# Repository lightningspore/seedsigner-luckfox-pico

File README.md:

# seedsigner-luckfox-pico
Port of the SeedSigner code to support the LuckFox Pico Linux board family. Since this device is still an embedded Linux device, like the Raspberry Pi, the changes are fairly minimal in order to access the buttons and the camera. This repo mostly pertains to the Buildroot OS build instructions, the KiCAD schematic and PCB design files, and 3D models of cases for the assembled device.

SeedSigner code fork: https://github.com/lightningspore/seedsigner/tree/0.8.5-luckfox

## Hardware Photos
_Most Recent Iteration: LuckFox Pico Mini B with no onboard SPI flash_

_Previous Iteration: LuckFox Pico Pro Max (More Flash, SPI Flash)_

## Demo Videos

### First Look: SeedSigner running on LuckFox Pico Linux devboard

## Materials Needed
Check out the shopping list for a parts list of various LuckFox-based hardware configurations: [here](docs/shopping_list.md)

These example builds can build a device for around $60.

## OS Image Build with Buildroot
The OS image is built using Buildroot in a Docker container. The complete build instructions, package requirements, and troubleshooting process are documented in [OS-build-instructions.md](docs/OS-build-instructions.md).

## Dev Machine Setup

### Install ADB
Developing for the LuckFox Pico device is quite convenient since the devices never connect to the internet and you can access the device shell using `adb`. You can push files back and forth to your dev machine, and you can access the device as a shell easily.
```
# mac
brew install homebrew/cask/android-platform-tools

# linux
sudo apt install android-tools-adb
```

### ADB Connection and Device Management

1. Connect to the device:
```
# List connected devices
adb devices

# Connect to device shell
adb shell
```

2. File Operations:
```
# Push files to device
adb push local_file.txt /remote/path/

# Sync the code repo for local development
adb push /repos/seedsigner/src /seedsigner

# Pull files from device
adb pull /seedsigner/config.json .

# List files on device
adb shell ls /path/to/directory
```

## Hardware Identification
Notice the left device has an empty PCB footprint pattern on it. This is where the optional SPI flash is soldered on. For the SeedSigner project we don't want permanent storage, so avoid devices with soldered SPI flash.

```
LEFT:  LuckFox Pico Mini A -> No Flash
RIGHT: LuckFox Pico Mini B -> Soldered Flash
```

## Flashing the Device

### Flash MicroSD Card
```
sudo dd bs=4M status=progress if=seedsigner-luckfox-pico-YYYYmmdd_hhmmss.img of=/dev/diskX
```
Replace `/dev/diskX` with your actual SD card device path.

## LuckFox Pico OS Modifications
We have forked the [LuckFox Pico SDK](https://github.com/lightningspore/luckfox-pico) in order to enable various hardware features like pull-up resistors, adjust video RAM, and other things.

### Camera Memory
The LuckFox devotes some of its memory for camera-related algorithms, but we don't use this feature. Particularly on the LuckFox Pico Mini device, which only has 64MB of RAM, it is beneficial for us to reclaim a bit of this memory.

Memory usage WITHOUT modification:
```bash
[root@luckfox ]# free -h
              total        used        free      shared  buff/cache   available
Mem:          33.0M       24.3M        1.4M      476.0K        7.3M        5.4M
Swap:             0           0           0
```

Memory usage WITH modification:
```bash
[root@luckfox ]# free -h
              total        used        free      shared  buff/cache   available
Mem:          53.0M       23.6M        1.9M      472.0K       27.5M       25.3M
Swap:             0           0           0
```

### Pull-up Resistors
Our current dev board has external pull-up resistors, since we didn't know how to enable these at the time, and it is always smart to plan ahead when designing PCBs. NOTE: Even with this commit and this change, the internal pull-ups don't seem to work.

### SPI Buffer Size
While it is possible to send SPI data in chunks, you can increase the SPI buffer size to slightly increase throughput, which is useful for larger displays.

### PWM Output
In order to control the LCD screen backlight and support true dimming of the display (instead of just changing the background color of the QR code, for example), we had to enable a PWM on a specific output pin.

## Support the Developer
If you find this project helpful and would like to support its development, you can buy me a coffee! Your support helps keep this project going and funds future improvements. Help decentralize Bitcoin hardware!

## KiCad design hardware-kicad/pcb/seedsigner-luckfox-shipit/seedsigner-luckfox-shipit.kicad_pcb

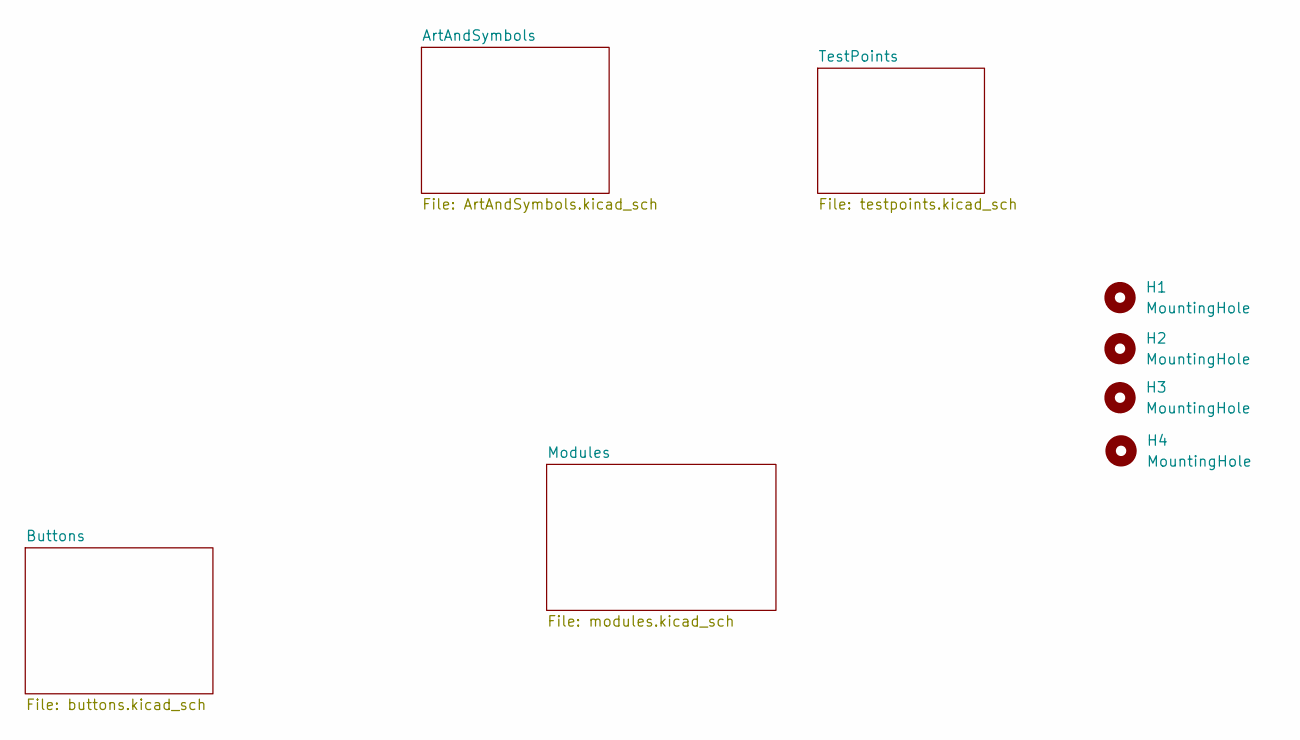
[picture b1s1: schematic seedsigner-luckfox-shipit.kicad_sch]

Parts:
H1, H2, H3, H4: MountingHole; MOUNT_HOLE_3MM

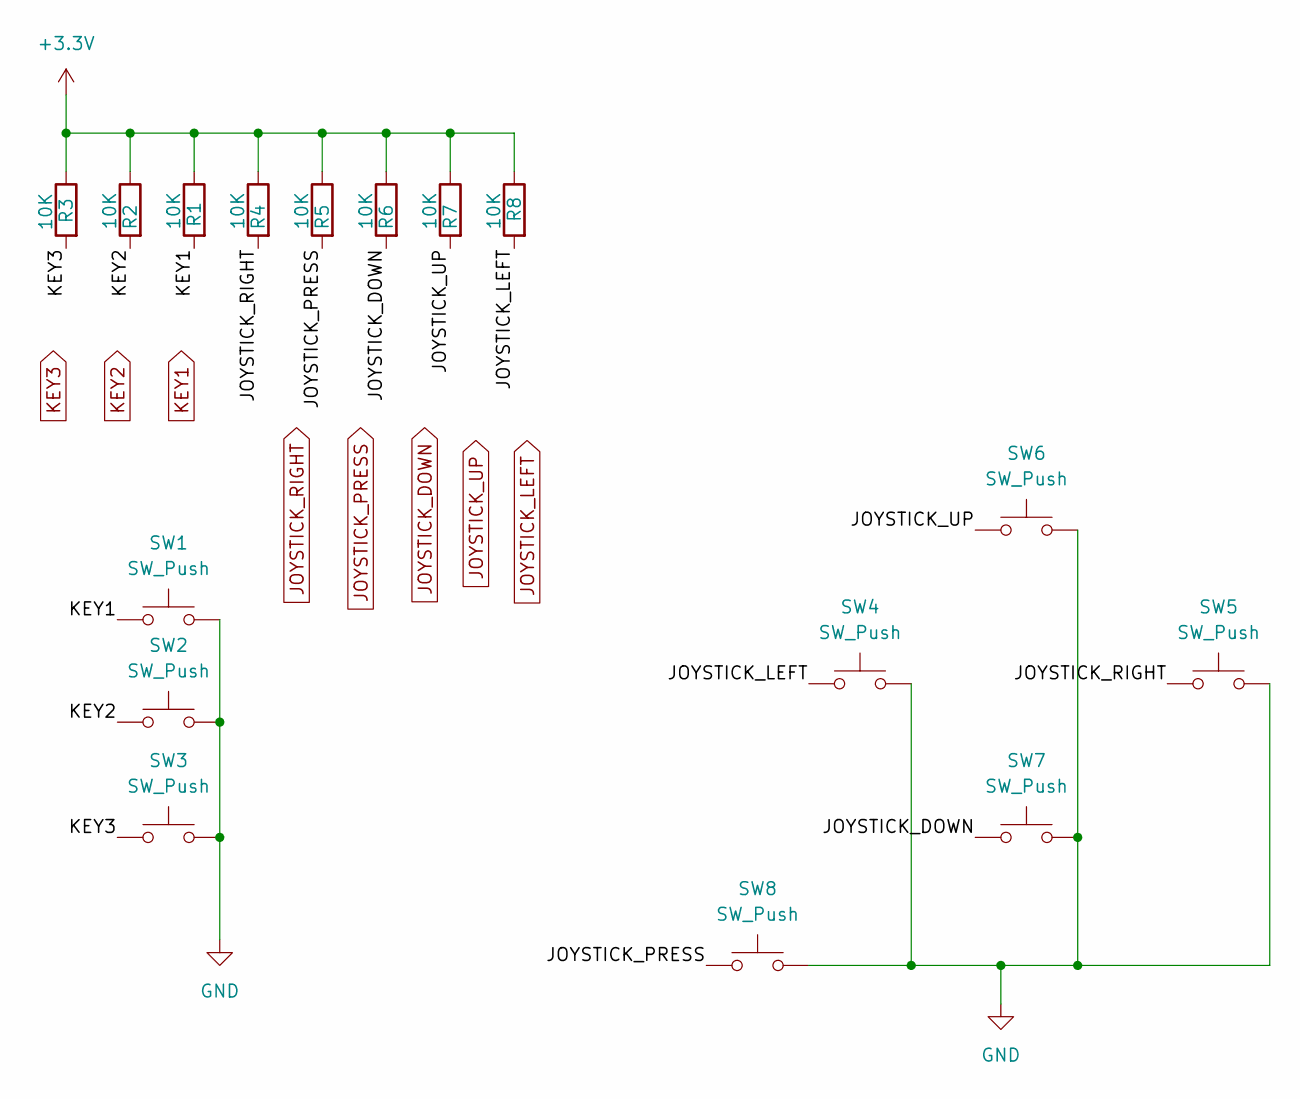
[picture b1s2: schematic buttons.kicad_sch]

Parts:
R1, R2, R3, R4, R5, R6, R7, R8: 10K; R_0805_2012Metric_Pad1.20x1.40mm_HandSolder
SW1, SW2, SW3, SW4, SW5, SW6, SW7, SW8: SW_Push; BTN_SPST_NO_PTH

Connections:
+3.3V: R1.1, R2.1, R3.1, R4.1, R5.1, R6.1, R7.1, R8.1; also elsewhere on the board
GND: SW1.2, SW2.2, SW3.2, SW4.2, SW5.2, SW6.2, SW7.2, SW8.2; also elsewhere on the board
JOYSTICK_DOWN: R6.2, SW7.1; also elsewhere on the board
JOYSTICK_LEFT: R8.2, SW4.1; also elsewhere on the board
JOYSTICK_PRESS: R5.2, SW8.1; also elsewhere on the board
JOYSTICK_RIGHT: R4.2, SW5.1; also elsewhere on the board
JOYSTICK_UP: R7.2, SW6.1; also elsewhere on the board
KEY1: R1.2, SW1.1; also elsewhere on the board
KEY2: R2.2, SW2.1; also elsewhere on the board
KEY3: R3.2, SW3.1; also elsewhere on the board

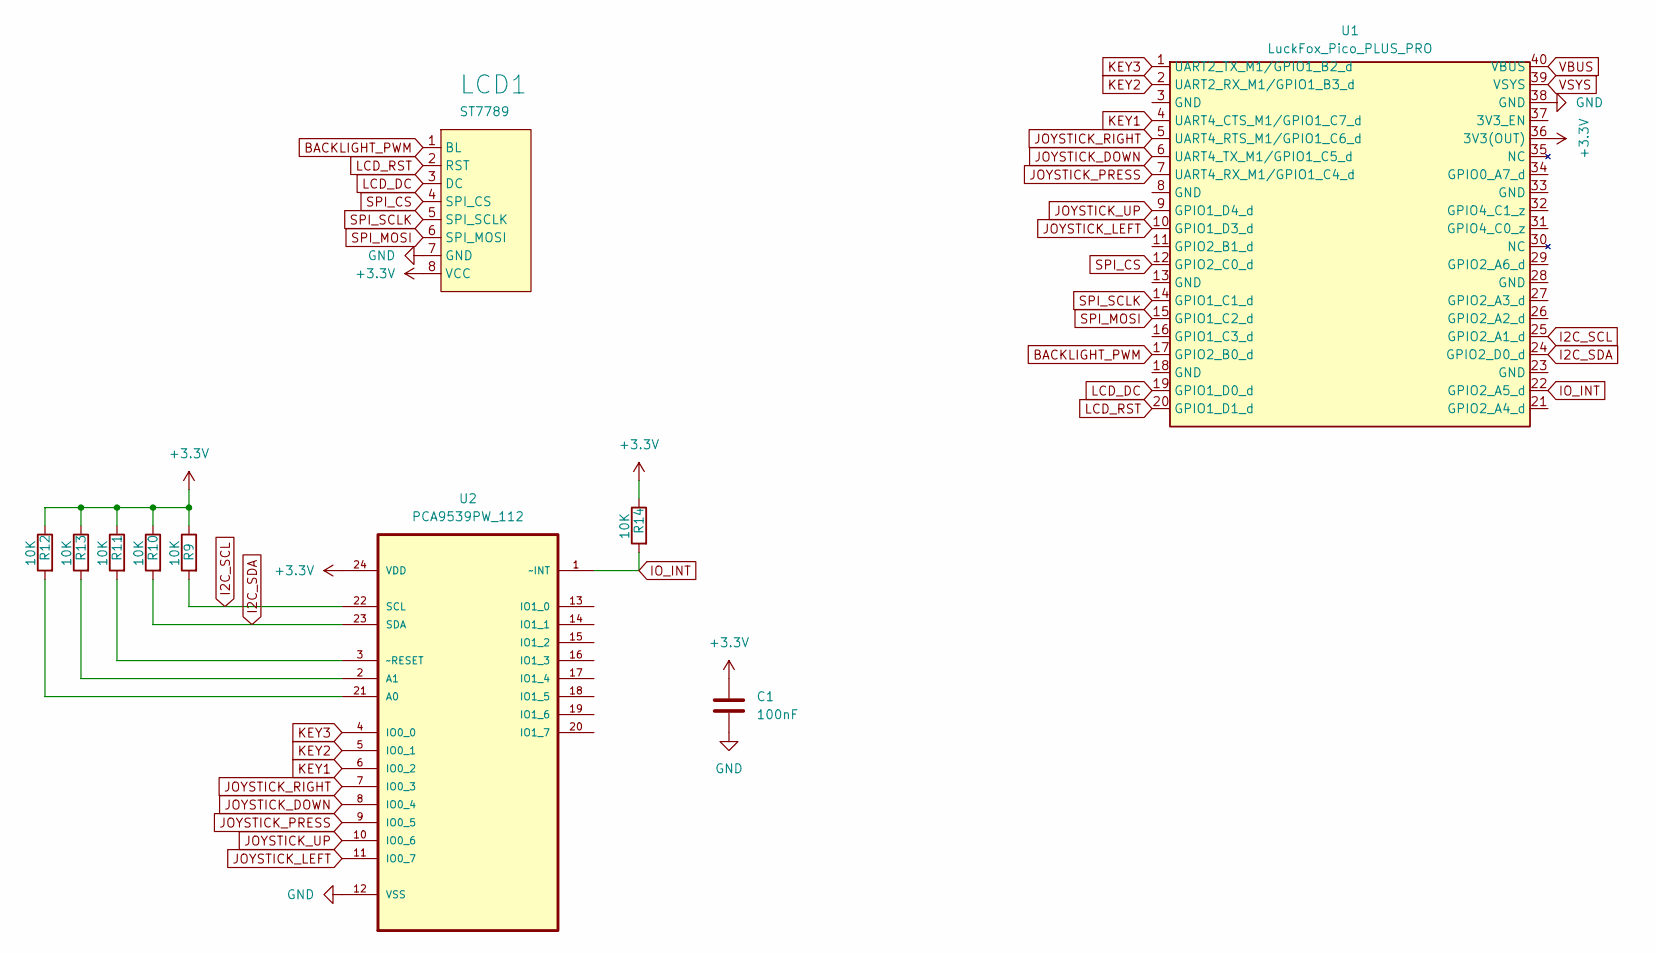
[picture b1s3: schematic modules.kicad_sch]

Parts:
C1: 100nF; C_0805_2012Metric_Pad1.18x1.45mm_HandSolder
LCD1: ST7789; ST7789_LCD_MOD1
R9, R10, R11, R12, R13, R14: 10K; R_0805_2012Metric_Pad1.20x1.40mm_HandSolder
U1: LuckFox_Pico_PLUS_PRO; LUCKFOX_PICO
U2: PCA9539PW_112; SOP65P640X110-24N; MPN PCA9539PW,112

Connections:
+3.3V: C1.1, LCD1.8 (VCC), R9.1, R10.1, R11.1, R12.1, R13.1, R14.1, U1.36 (3V3(OUT)), U2.24 (VDD); also elsewhere on the board
BACKLIGHT_PWM: LCD1.1 (BL), U1.17 (GPIO2_B0_d)
GND: C1.2, LCD1.7 (GND), U1.38 (GND), U2.12 (VSS); also elsewhere on the board
I2C_SCL: R9.2, U1.25 (GPIO2_A1_d), U2.22 (SCL)
I2C_SDA: R10.2, U1.24 (GPIO2_D0_d), U2.23 (SDA)
IO_INT: R14.2, U1.22 (GPIO2_A5_d), U2.1 (~INT)
JOYSTICK_DOWN: U1.6 (UART4_TX_M1/GPIO1_C5_d), U2.8 (IO0_4); also elsewhere on the board
JOYSTICK_LEFT: U1.10 (GPIO1_D3_d), U2.11 (IO0_7); also elsewhere on the board
JOYSTICK_PRESS: U1.7 (UART4_RX_M1/GPIO1_C4_d), U2.9 (IO0_5); also elsewhere on the board
JOYSTICK_RIGHT: U1.5 (UART4_RTS_M1/GPIO1_C6_d), U2.7 (IO0_3); also elsewhere on the board
JOYSTICK_UP: U1.9 (GPIO1_D4_d), U2.10 (IO0_6); also elsewhere on the board
KEY1: U1.4 (UART4_CTS_M1/GPIO1_C7_d), U2.6 (IO0_2); also elsewhere on the board
KEY2: U1.2 (UART2_RX_M1/GPIO1_B3_d), U2.5 (IO0_1); also elsewhere on the board
KEY3: U1.1 (UART2_TX_M1/GPIO1_B2_d), U2.4 (IO0_0); also elsewhere on the board
LCD_DC: LCD1.3 (DC), U1.19 (GPIO1_D0_d)
LCD_RST: LCD1.2 (RST), U1.20 (GPIO1_D1_d)
unnamed: R12.2, U2.21 (A0)
unnamed: R13.2, U2.2 (A1)
unnamed: R11.2, U2.3 (~RESET)
SPI_CS: LCD1.4 (SPI_CS), U1.12 (GPIO2_C0_d)
SPI_MOSI: LCD1.6 (SPI_MOSI), U1.15 (GPIO1_C2_d)
SPI_SCLK: LCD1.5 (SPI_SCLK), U1.14 (GPIO1_C1_d)
VBUS: U1.40 (VBUS); also elsewhere on the board
VSYS: U1.39 (VSYS); also elsewhere on the board

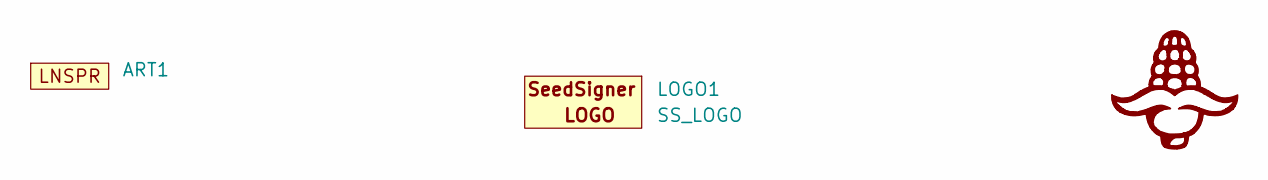
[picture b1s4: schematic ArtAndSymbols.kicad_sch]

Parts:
ART1: LightningSpore_Logo
LOGO1: SS_LOGO; seedsigner-logo-small
LOGO2: CORN-LOGO; corn-logo

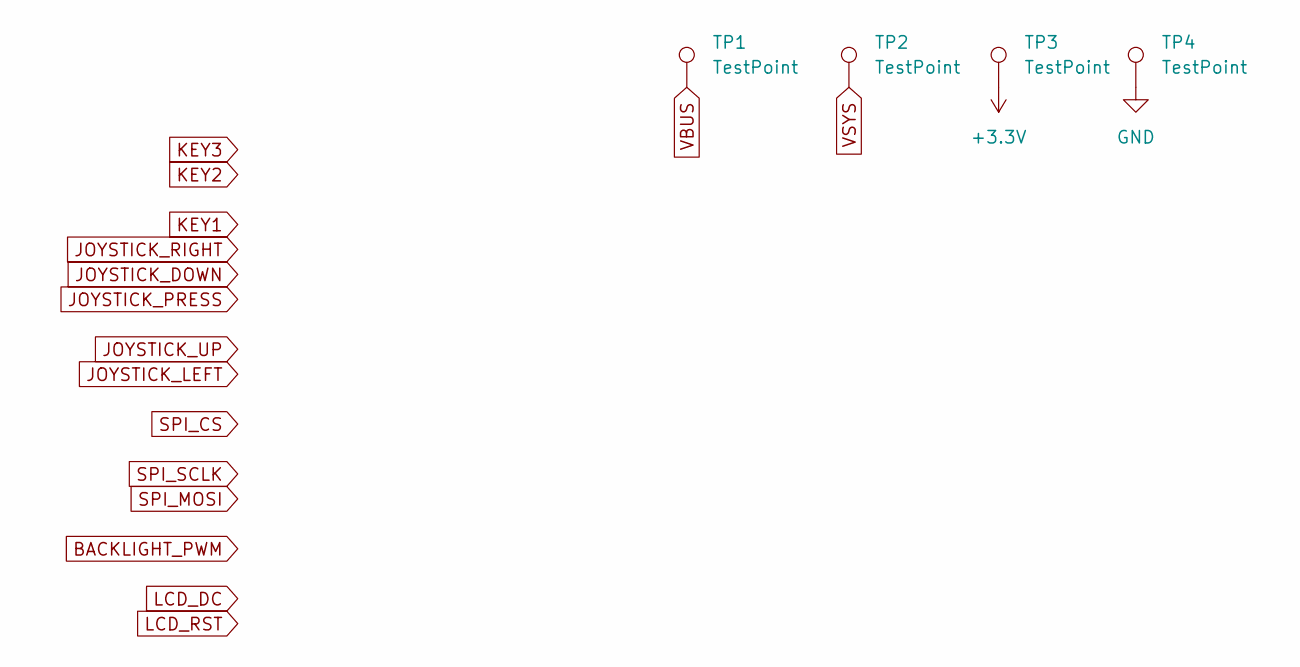
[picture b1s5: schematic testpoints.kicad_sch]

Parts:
TP1, TP2, TP3, TP4: TestPoint; TestPoint_Pad_1.5x1.5mm

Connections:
+3.3V: TP3.1; also elsewhere on the board
GND: TP4.1; also elsewhere on the board
VBUS: TP1.1; also elsewhere on the board
VSYS: TP2.1; also elsewhere on the board

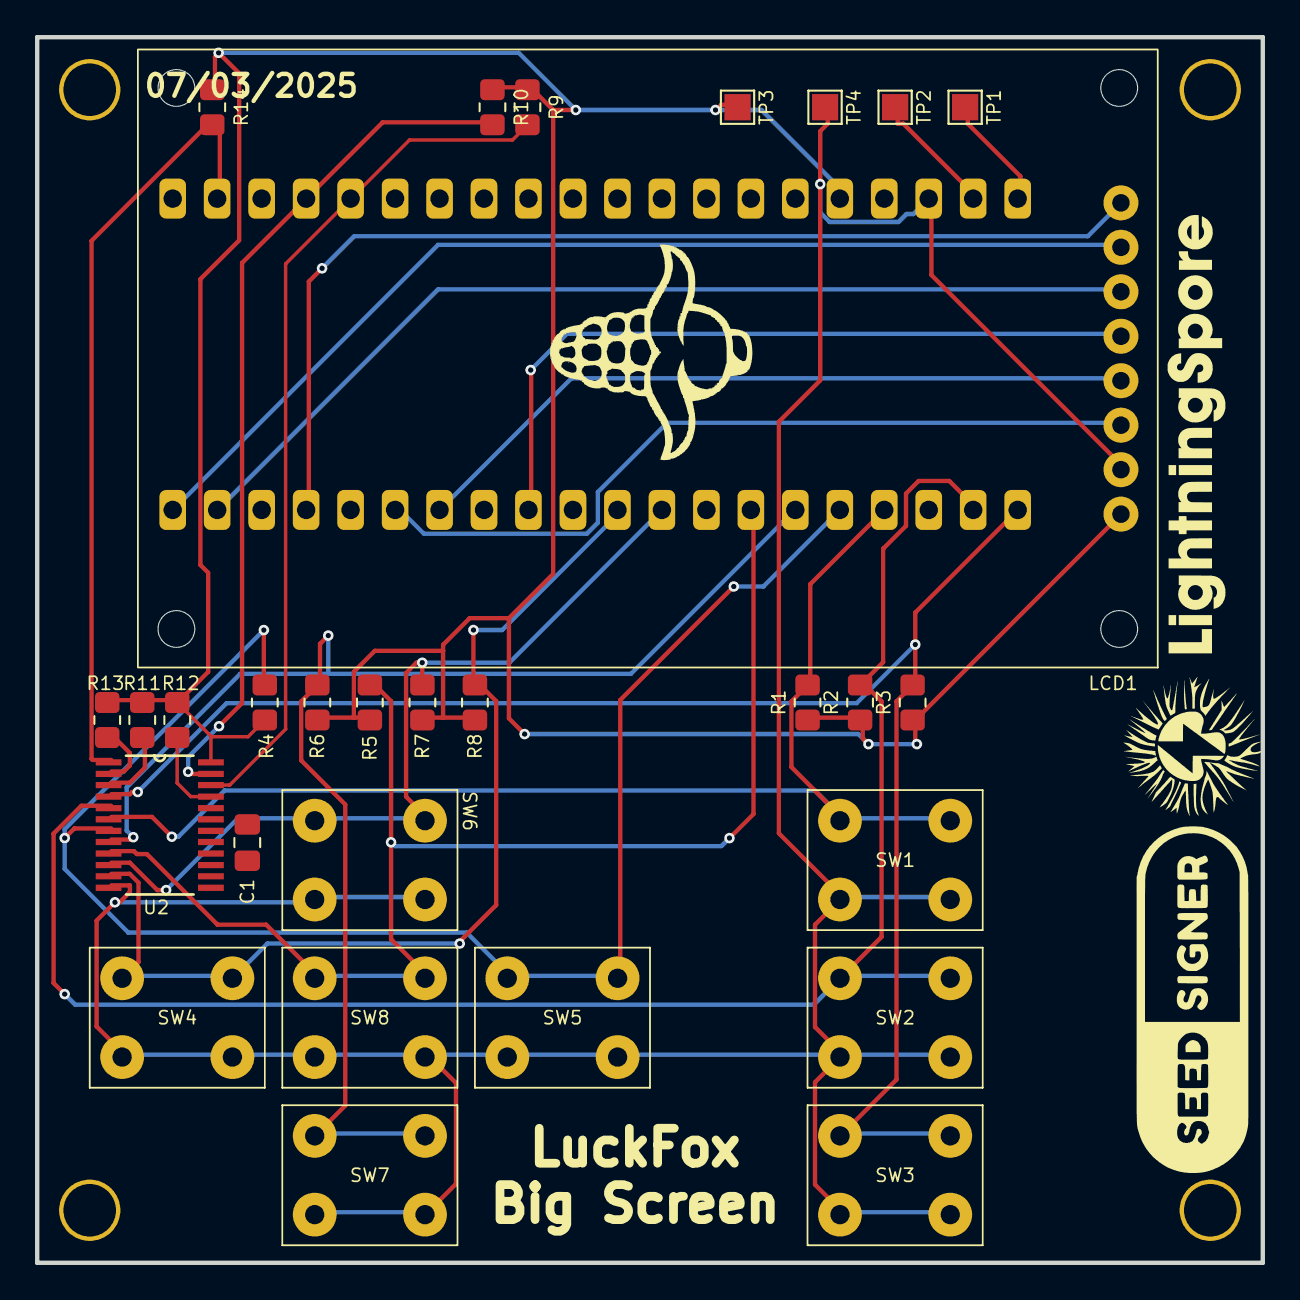
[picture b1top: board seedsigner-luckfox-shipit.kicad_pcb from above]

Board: 2 copper layers, 70.0 x 70.0 mm, 37 parts (1 on the bottom side), 24 nets.

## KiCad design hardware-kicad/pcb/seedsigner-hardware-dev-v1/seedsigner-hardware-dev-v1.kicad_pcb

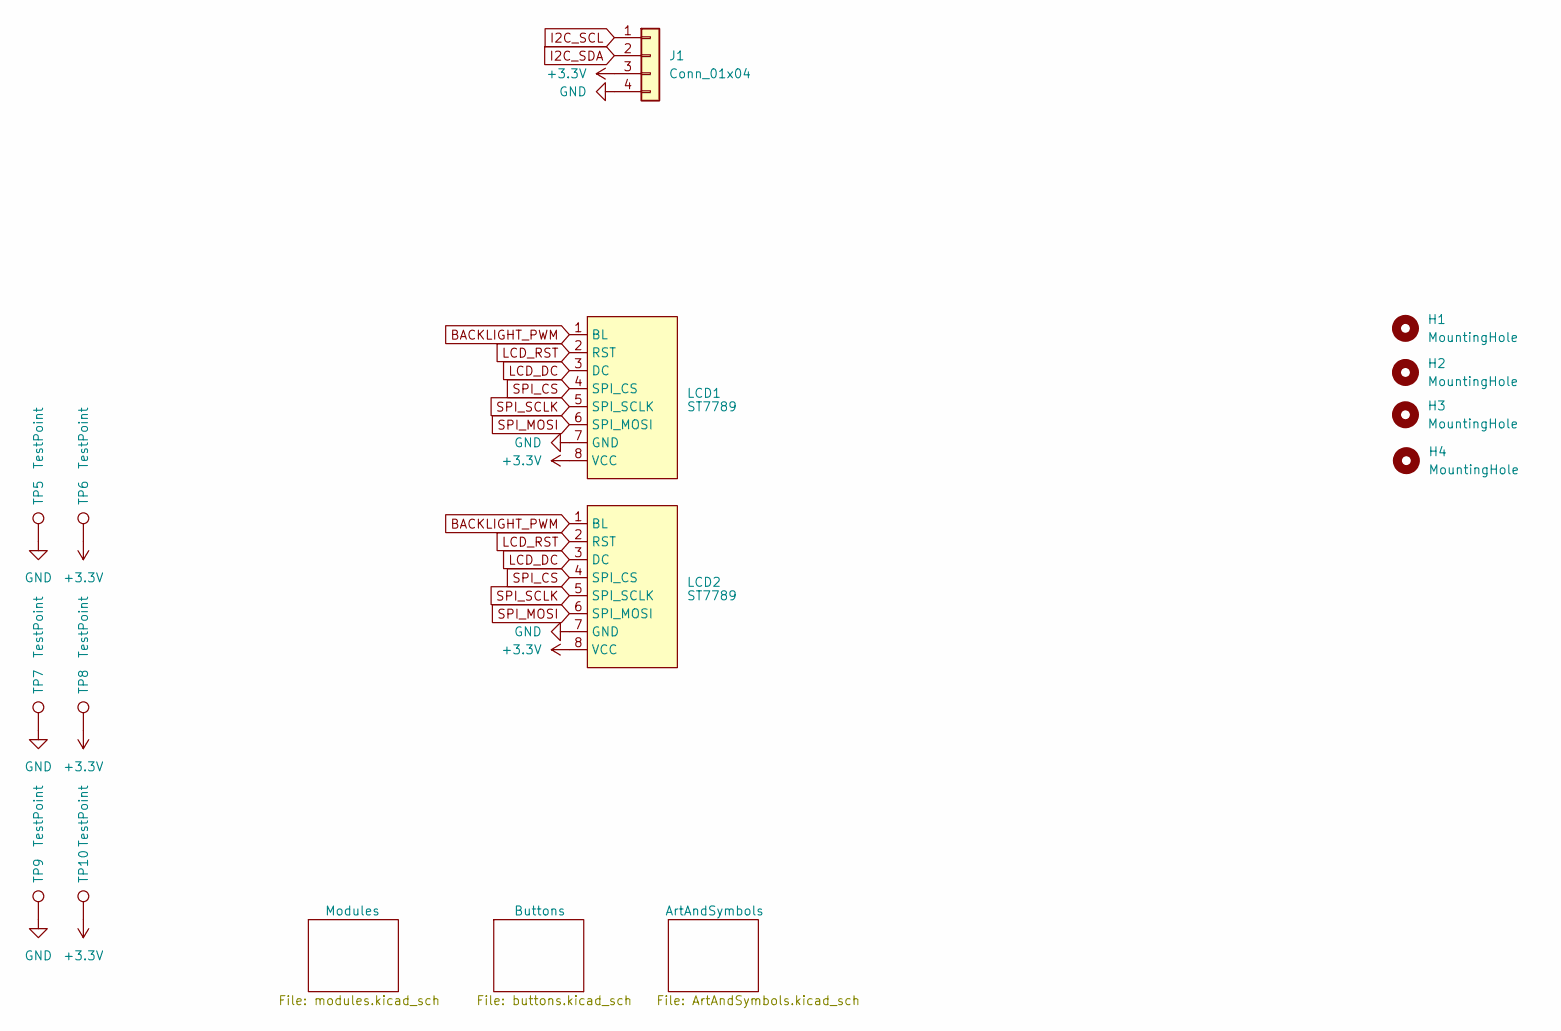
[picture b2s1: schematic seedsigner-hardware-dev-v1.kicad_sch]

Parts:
H1, H2, H3, H4: MountingHole; MOUNT_HOLE_3MM
J1: Conn_01x04; NS-Tech_Grove_1x04_P2mm_Vertical
LCD1, LCD2: ST7789; PinHeader_1x08_P2.54mm_Vertical
TP5, TP6, TP7, TP8, TP9, TP10: TestPoint; TestPoint_Pad_D1.0mm

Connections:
+3.3V: J1.3, LCD1.8 (VCC), LCD2.8 (VCC), TP6.1, TP8.1, TP10.1; also elsewhere on the board
BACKLIGHT_PWM: LCD1.1 (BL), LCD2.1 (BL); also elsewhere on the board
GND: J1.4, LCD1.7 (GND), LCD2.7 (GND), TP5.1, TP7.1, TP9.1; also elsewhere on the board
I2C_SCL: J1.1; also elsewhere on the board
I2C_SDA: J1.2; also elsewhere on the board
LCD_DC: LCD1.3 (DC), LCD2.3 (DC); also elsewhere on the board
LCD_RST: LCD1.2 (RST), LCD2.2 (RST); also elsewhere on the board
SPI_CS: LCD1.4 (SPI_CS), LCD2.4 (SPI_CS); also elsewhere on the board
SPI_MOSI: LCD1.6 (SPI_MOSI), LCD2.6 (SPI_MOSI); also elsewhere on the board
SPI_SCLK: LCD1.5 (SPI_SCLK), LCD2.5 (SPI_SCLK); also elsewhere on the board

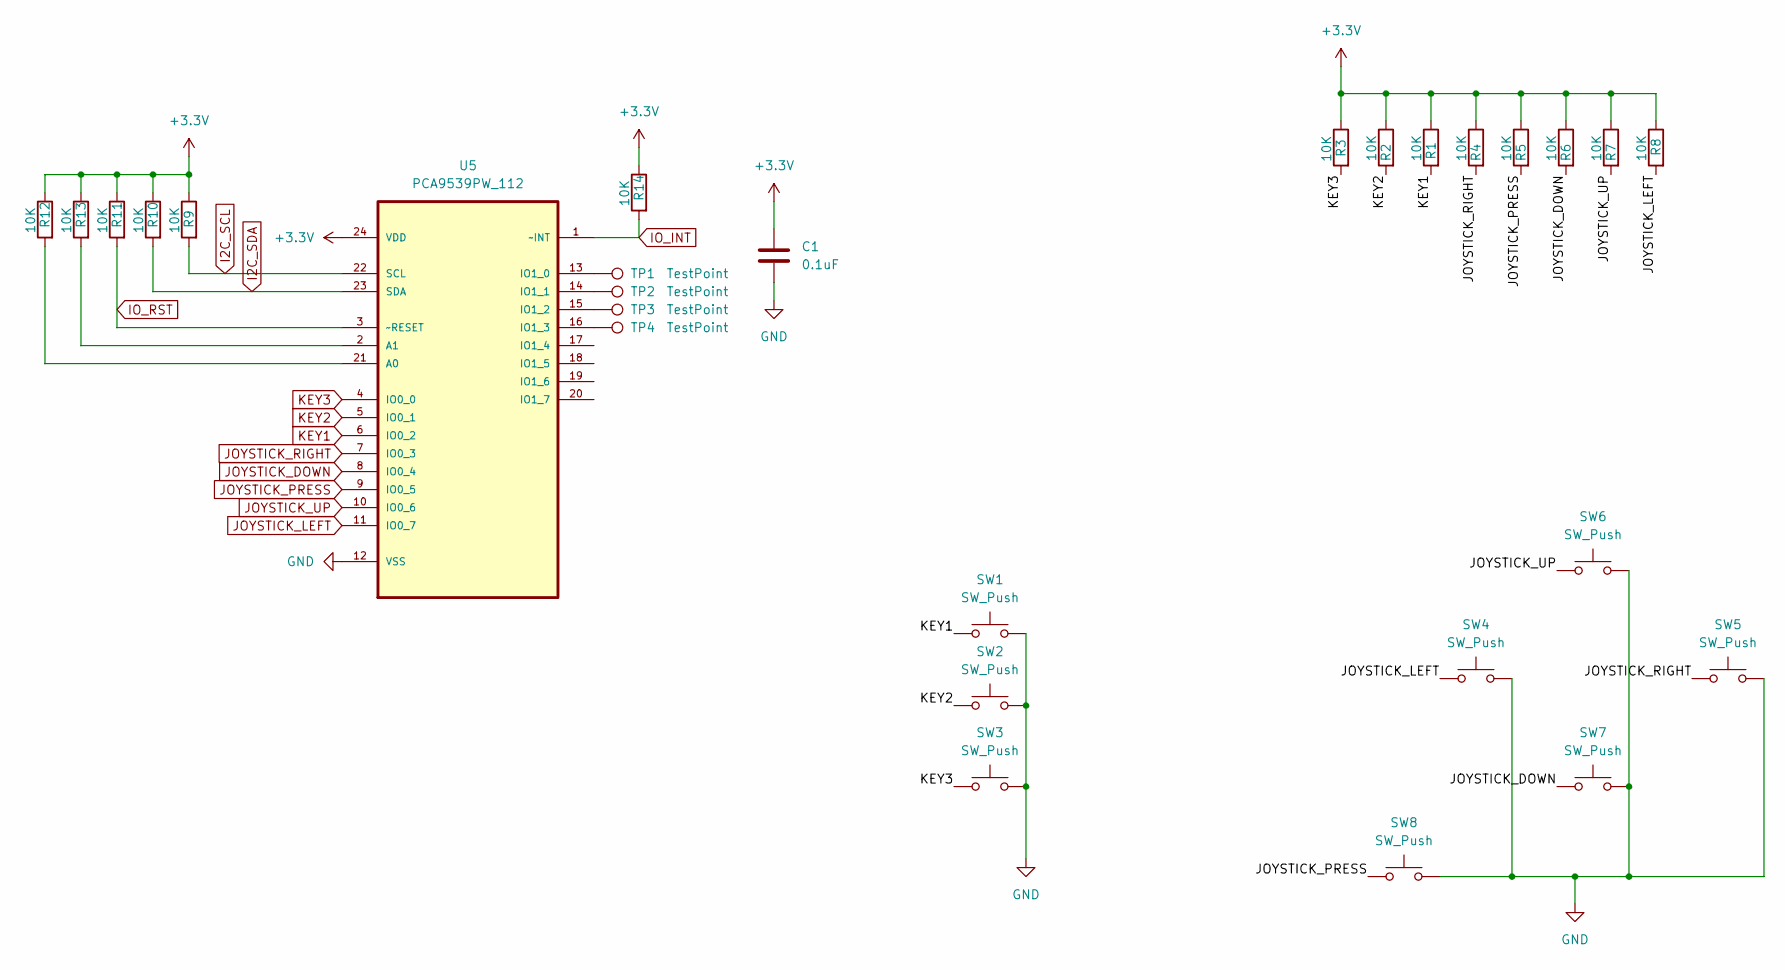
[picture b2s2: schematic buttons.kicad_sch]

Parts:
C1: 0.1uF; C_0805_2012Metric_Pad1.18x1.45mm_HandSolder
R1, R2, R3, R4, R5, R6, R7, R8, R9, R10, R11, R12, R13, R14: 10K; R_0805_2012Metric_Pad1.20x1.40mm_HandSolder
SW1, SW2, SW3, SW4, SW5, SW6, SW7, SW8: SW_Push; BTN_SPST_NO_PTH
TP1, TP2, TP3, TP4: TestPoint; TestPoint_Pad_D1.0mm
U5: PCA9539PW_112; SOP65P640X110-24N; MPN PCA9539PW,112

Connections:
+3.3V: C1.1, R1.1, R2.1, R3.1, R4.1, R5.1, R6.1, R7.1, R8.1, R9.1, R10.1, R11.1, R12.1, R13.1, R14.1, U5.24 (VDD); also elsewhere on the board
GND: C1.2, SW1.2, SW2.2, SW3.2, SW4.2, SW5.2, SW6.2, SW7.2, SW8.2, U5.12 (VSS); also elsewhere on the board
I2C_SCL: R9.2, U5.22 (SCL); also elsewhere on the board
I2C_SDA: R10.2, U5.23 (SDA); also elsewhere on the board
IO_INT: R14.2, U5.1 (~INT); also elsewhere on the board
IO_RST: R11.2, U5.3 (~RESET); also elsewhere on the board
JOYSTICK_DOWN: R6.2, SW7.1, U5.8 (IO0_4); also elsewhere on the board
JOYSTICK_LEFT: R8.2, SW4.1, U5.11 (IO0_7); also elsewhere on the board
JOYSTICK_PRESS: R5.2, SW8.1, U5.9 (IO0_5); also elsewhere on the board
JOYSTICK_RIGHT: R4.2, SW5.1, U5.7 (IO0_3); also elsewhere on the board
JOYSTICK_UP: R7.2, SW6.1, U5.10 (IO0_6); also elsewhere on the board
KEY1: R1.2, SW1.1, U5.6 (IO0_2); also elsewhere on the board
KEY2: R2.2, SW2.1, U5.5 (IO0_1); also elsewhere on the board
KEY3: R3.2, SW3.1, U5.4 (IO0_0); also elsewhere on the board
unnamed: R12.2, U5.21 (A0)
unnamed: R13.2, U5.2 (A1)
unnamed: TP1.1, U5.13 (IO1_0)
unnamed: TP2.1, U5.14 (IO1_1)
unnamed: TP3.1, U5.15 (IO1_2)
unnamed: TP4.1, U5.16 (IO1_3)

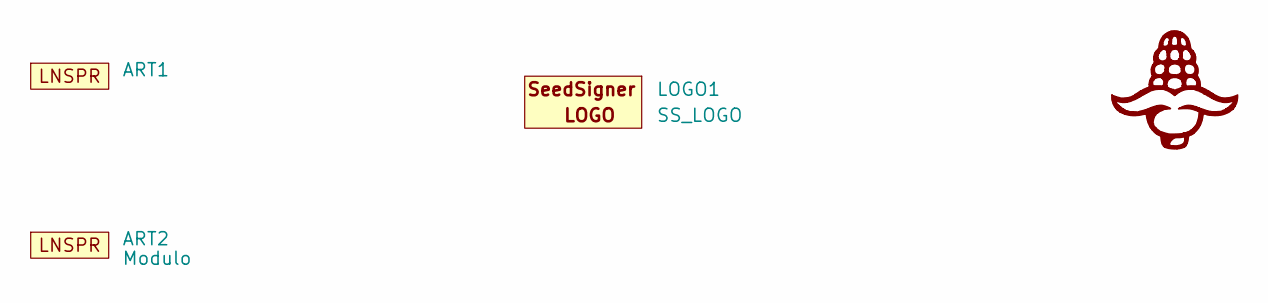
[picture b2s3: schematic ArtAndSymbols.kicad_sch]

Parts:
ART1: LightningSpore_Logo
ART2: Modulo; modulo-1
LOGO1: SS_LOGO; seedsigner-logo-small
LOGO2: CORN-LOGO; corn-logo

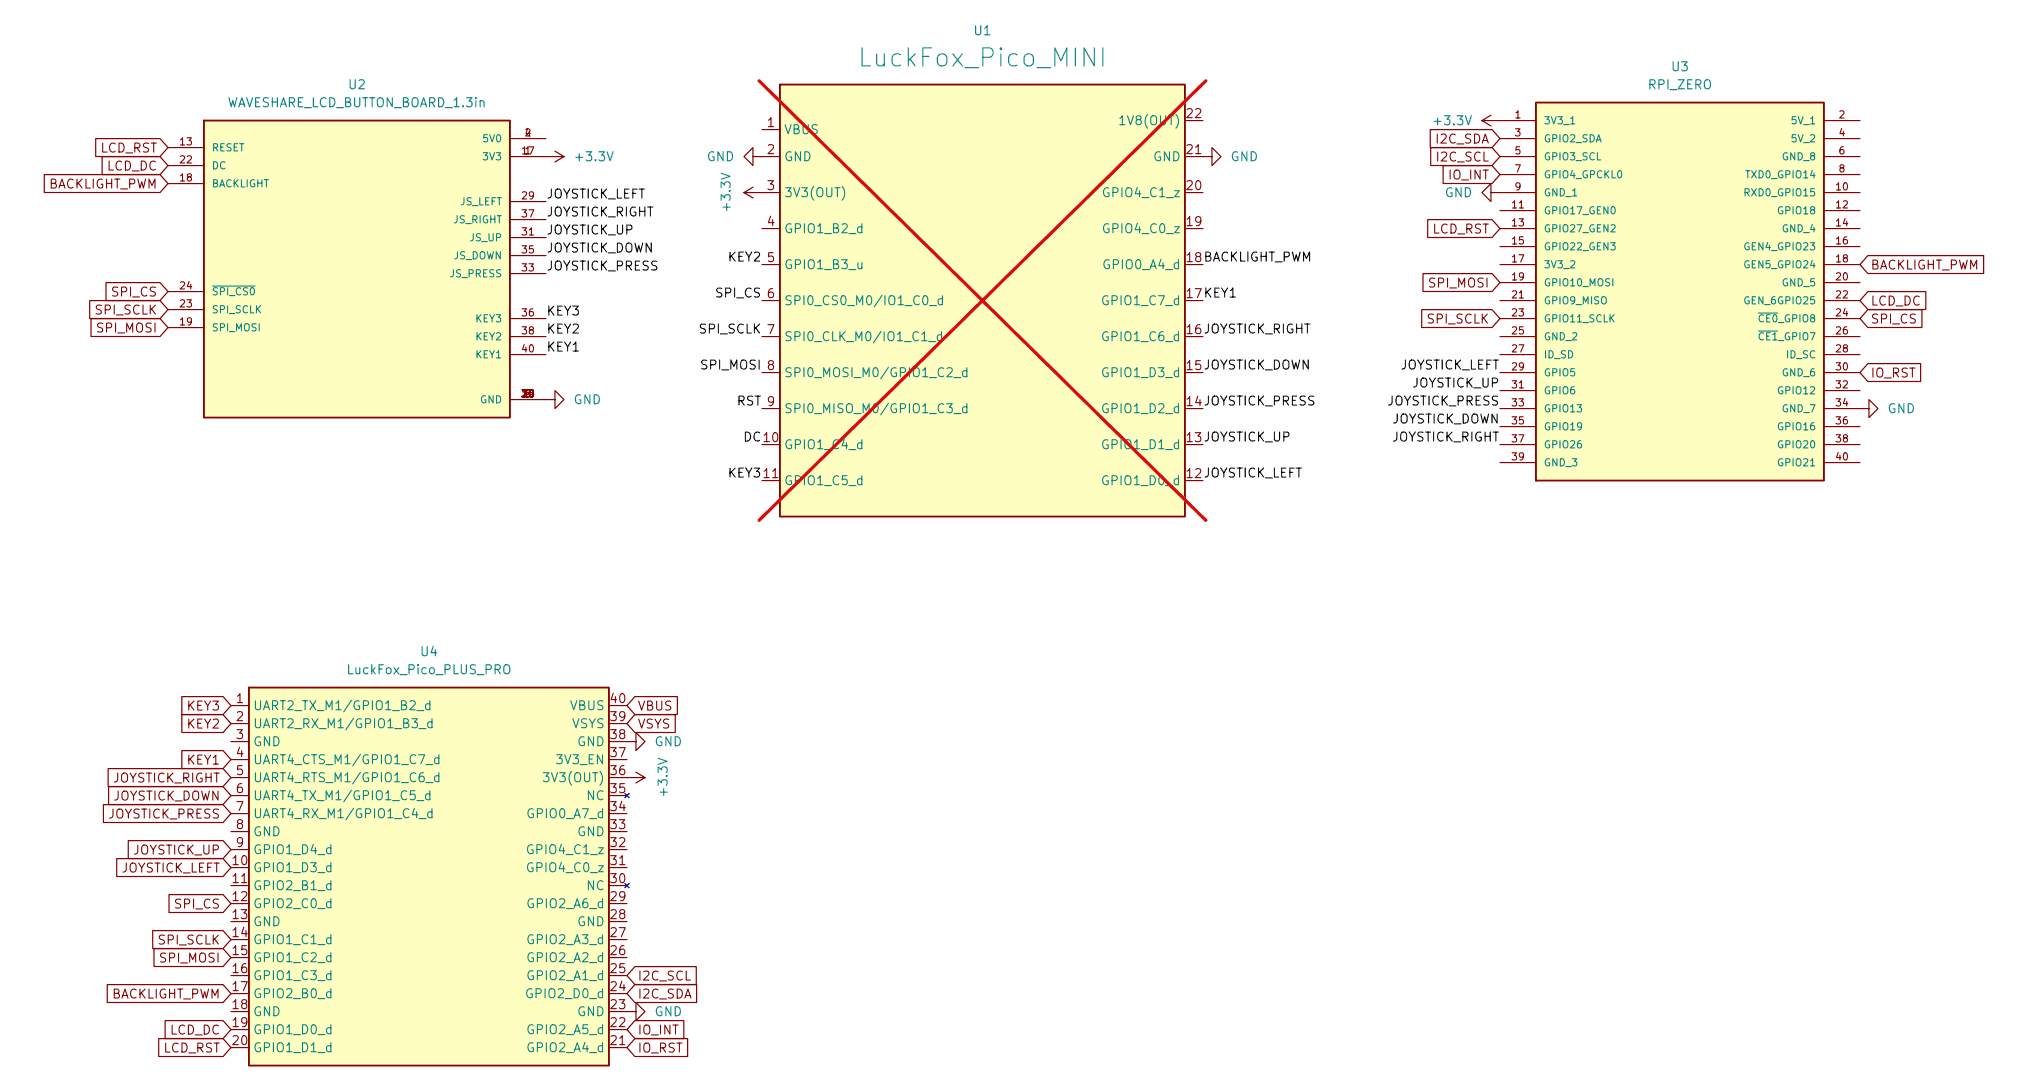
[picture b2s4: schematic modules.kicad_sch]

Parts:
U1: LuckFox_Pico_MINI; LUCKFOX_PICO_MINI; not fitted
U2: WAVESHARE_LCD_BUTTON_BOARD_1.3in; WAVESHARE_LCD_BUTTON
U3: RPI_ZERO; RPi_Zero
U4: LuckFox_Pico_PLUS_PRO; LUCKFOX_PICO

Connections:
+3.3V: U1.3 (3V3(OUT)), U2.1 (3V3), U2.17 (3V3), U3.1 (3V3_1), U4.36 (3V3(OUT)); also elsewhere on the board
BACKLIGHT_PWM: U2.18 (BACKLIGHT), U3.18 (GEN5_GPIO24), U4.17 (GPIO2_B0_d); also elsewhere on the board
GND: U1.2 (GND), U1.21 (GND), U2.6 (GND), U2.9 (GND), U2.14 (GND), U2.20 (GND), U2.25 (GND), U2.30 (GND), U2.34 (GND), U2.39 (GND), U3.9 (GND_1), U3.34 (GND_7), U4.23 (GND), U4.38 (GND); also elsewhere on the board
I2C_SCL: U3.5 (GPIO3_SCL), U4.25 (GPIO2_A1_d); also elsewhere on the board
I2C_SDA: U3.3 (GPIO2_SDA), U4.24 (GPIO2_D0_d); also elsewhere on the board
IO_INT: U3.7 (GPIO4_GPCKL0), U4.22 (GPIO2_A5_d); also elsewhere on the board
IO_RST: U3.30 (GND_6), U4.21 (GPIO2_A4_d); also elsewhere on the board
JOYSTICK_DOWN: U1.15 (GPIO1_D3_d), U2.35 (JS_DOWN), U3.35 (GPIO19), U4.6 (UART4_TX_M1/GPIO1_C5_d); also elsewhere on the board
JOYSTICK_LEFT: U1.12 (GPIO1_D0_d), U2.29 (JS_LEFT), U3.29 (GPIO5), U4.10 (GPIO1_D3_d); also elsewhere on the board
JOYSTICK_PRESS: U1.14 (GPIO1_D2_d), U2.33 (JS_PRESS), U3.33 (GPIO13), U4.7 (UART4_RX_M1/GPIO1_C4_d); also elsewhere on the board
JOYSTICK_RIGHT: U1.16 (GPIO1_C6_d), U2.37 (JS_RIGHT), U3.37 (GPIO26), U4.5 (UART4_RTS_M1/GPIO1_C6_d); also elsewhere on the board
JOYSTICK_UP: U1.13 (GPIO1_D1_d), U2.31 (JS_UP), U3.31 (GPIO6), U4.9 (GPIO1_D4_d); also elsewhere on the board
KEY1: U1.17 (GPIO1_C7_d), U2.40 (KEY1), U4.4 (UART4_CTS_M1/GPIO1_C7_d); also elsewhere on the board
KEY2: U1.5 (GPIO1_B3_u), U2.38 (KEY2), U4.2 (UART2_RX_M1/GPIO1_B3_d); also elsewhere on the board
KEY3: U1.11 (GPIO1_C5_d), U2.36 (KEY3), U4.1 (UART2_TX_M1/GPIO1_B2_d); also elsewhere on the board
LCD_DC: U2.22 (DC), U3.22 (GEN_6GPIO25), U4.19 (GPIO1_D0_d); also elsewhere on the board
LCD_RST: U2.13 (RESET), U3.13 (GPIO27_GEN2), U4.20 (GPIO1_D1_d); also elsewhere on the board
unnamed: U2.2 (5V0), U2.4 (5V0)
SPI_CS: U2.24 (~SPI_CS0), U3.24 (~CE0_GPIO8), U4.12 (GPIO2_C0_d); also elsewhere on the board
SPI_MOSI: U2.19 (SPI_MOSI), U3.19 (GPIO10_MOSI), U4.15 (GPIO1_C2_d); also elsewhere on the board
SPI_SCLK: U2.23 (SPI_SCLK), U3.23 (GPIO11_SCLK), U4.14 (GPIO1_C1_d); also elsewhere on the board
VBUS: U4.40 (VBUS)
VSYS: U4.39 (VSYS)

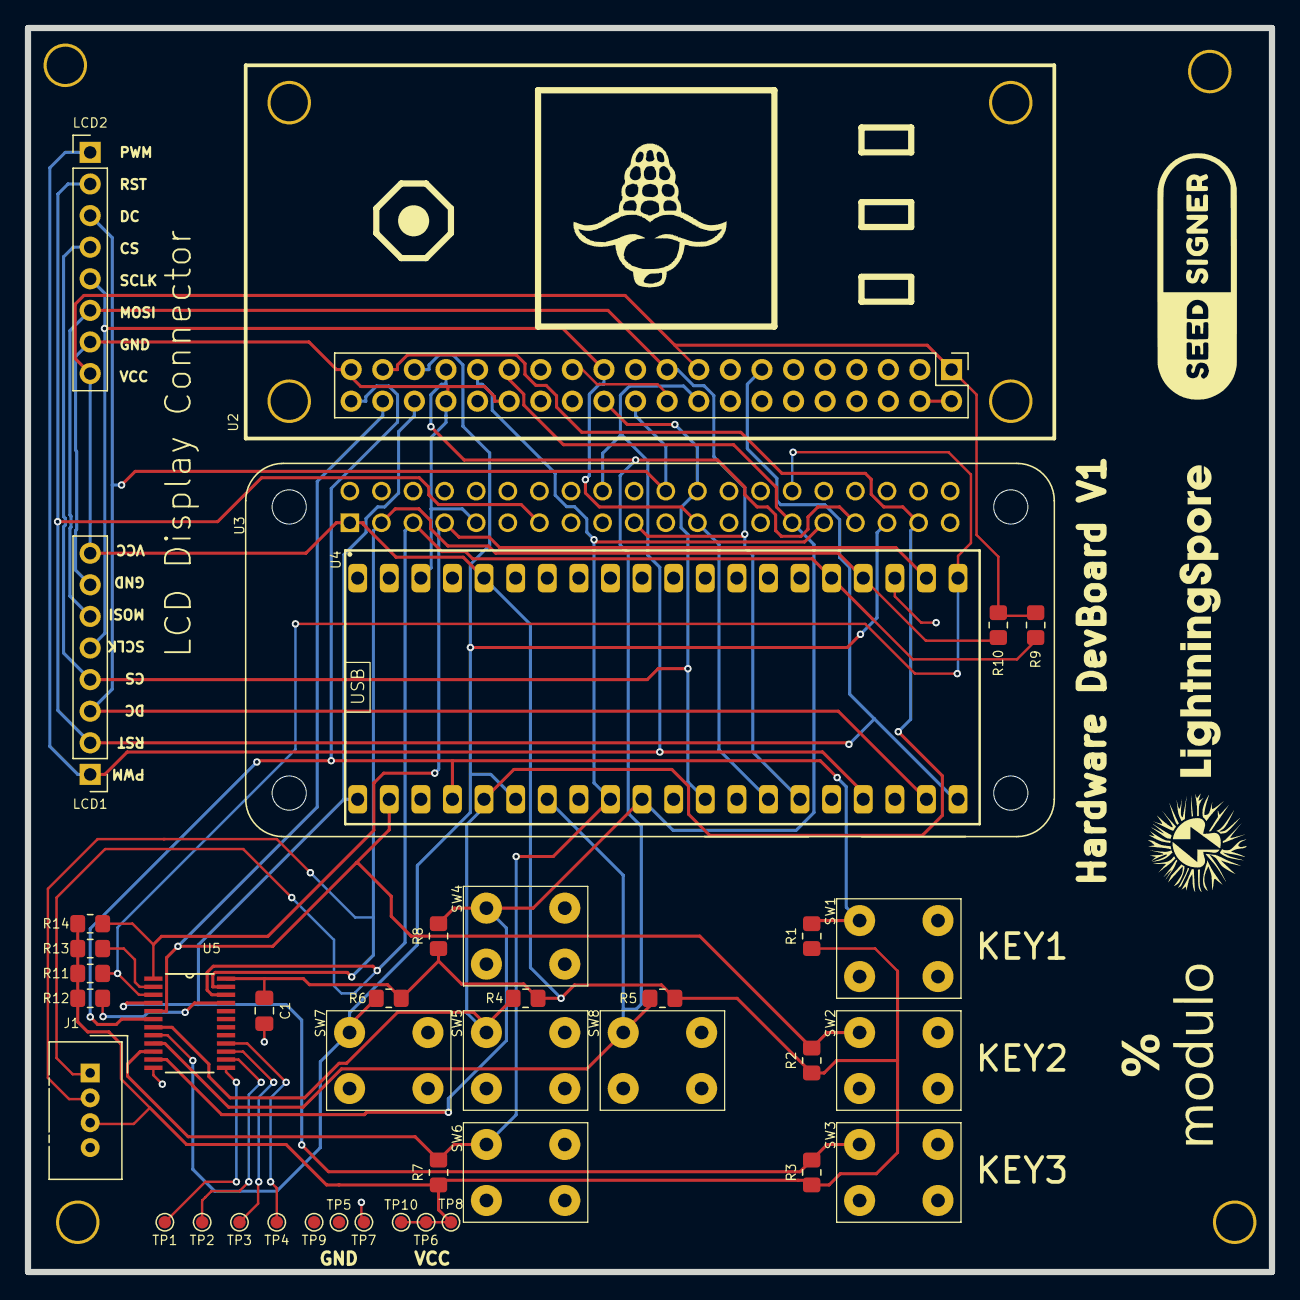
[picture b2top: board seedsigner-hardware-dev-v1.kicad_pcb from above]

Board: 2 copper layers, 100.0 x 100.0 mm, 48 parts (0 on the bottom side), 27 nets.

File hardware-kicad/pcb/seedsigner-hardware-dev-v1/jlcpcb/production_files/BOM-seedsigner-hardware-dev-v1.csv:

Comment,Designator,Footprint,LCSC,Quantity
PCA9539PW_112,U5,SOP65P640X110-24N,C129516,1
Conn_01x04,J1,NS-Tech_Grove_1x04_P2mm_Vertical,C157926,1
10K,"R1,R10,R11,R12,R13,R14,R2,R3,R4,R5,R6,R7,R8,R9",R_0805_2012Metric_Pad1.20x1.40mm_HandSolder,C17414,14
ST7789,"LCD1,LCD2",PinHeader_1x08_P2.54mm_Vertical,C190820,2
LuckFox_Pico_PLUS_PRO,"U4,U6",LUCKFOX_PICO,C25503124,1
RPI_ZERO,U3,RPi_Zero,C2685093,1
0.1uF,C1,C_0805_2012Metric_Pad1.18x1.45mm_HandSolder,C49678,1
WAVESHARE_LCD_BUTTON_BOARD_1.3in,U2,WAVESHARE_LCD_BUTTON,C5224014,1
SW_Push,SW5,BTN_SPST_NO_PTH,,1
TestPoint,TP6,TestPoint_Pad_D1.0mm,,1
SW_Push,SW6,BTN_SPST_NO_PTH,,1
SW_Push,SW2,BTN_SPST_NO_PTH,,1
TestPoint,TP4,TestPoint_Pad_D1.0mm,,1
SW_Push,SW3,BTN_SPST_NO_PTH,,1
TestPoint,TP2,TestPoint_Pad_D1.0mm,,1
SW_Push,SW7,BTN_SPST_NO_PTH,,1
SW_Push,SW1,BTN_SPST_NO_PTH,,1
TestPoint,TP1,TestPoint_Pad_D1.0mm,,1
TestPoint,TP3,TestPoint_Pad_D1.0mm,,1
SW_Push,SW8,BTN_SPST_NO_PTH,,1
TestPoint,TP5,TestPoint_Pad_D1.0mm,,1
SW_Push,SW4,BTN_SPST_NO_PTH,,1
TestPoint,TP9,TestPoint_Pad_D1.0mm,,1
TestPoint,TP7,TestPoint_Pad_D1.0mm,,1
TestPoint,TP10,TestPoint_Pad_D1.0mm,,1
TestPoint,TP8,TestPoint_Pad_D1.0mm,,1
